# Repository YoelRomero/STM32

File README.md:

https://digole.com/tools/PicturetoC_Hex_converter.php
ILI_9341

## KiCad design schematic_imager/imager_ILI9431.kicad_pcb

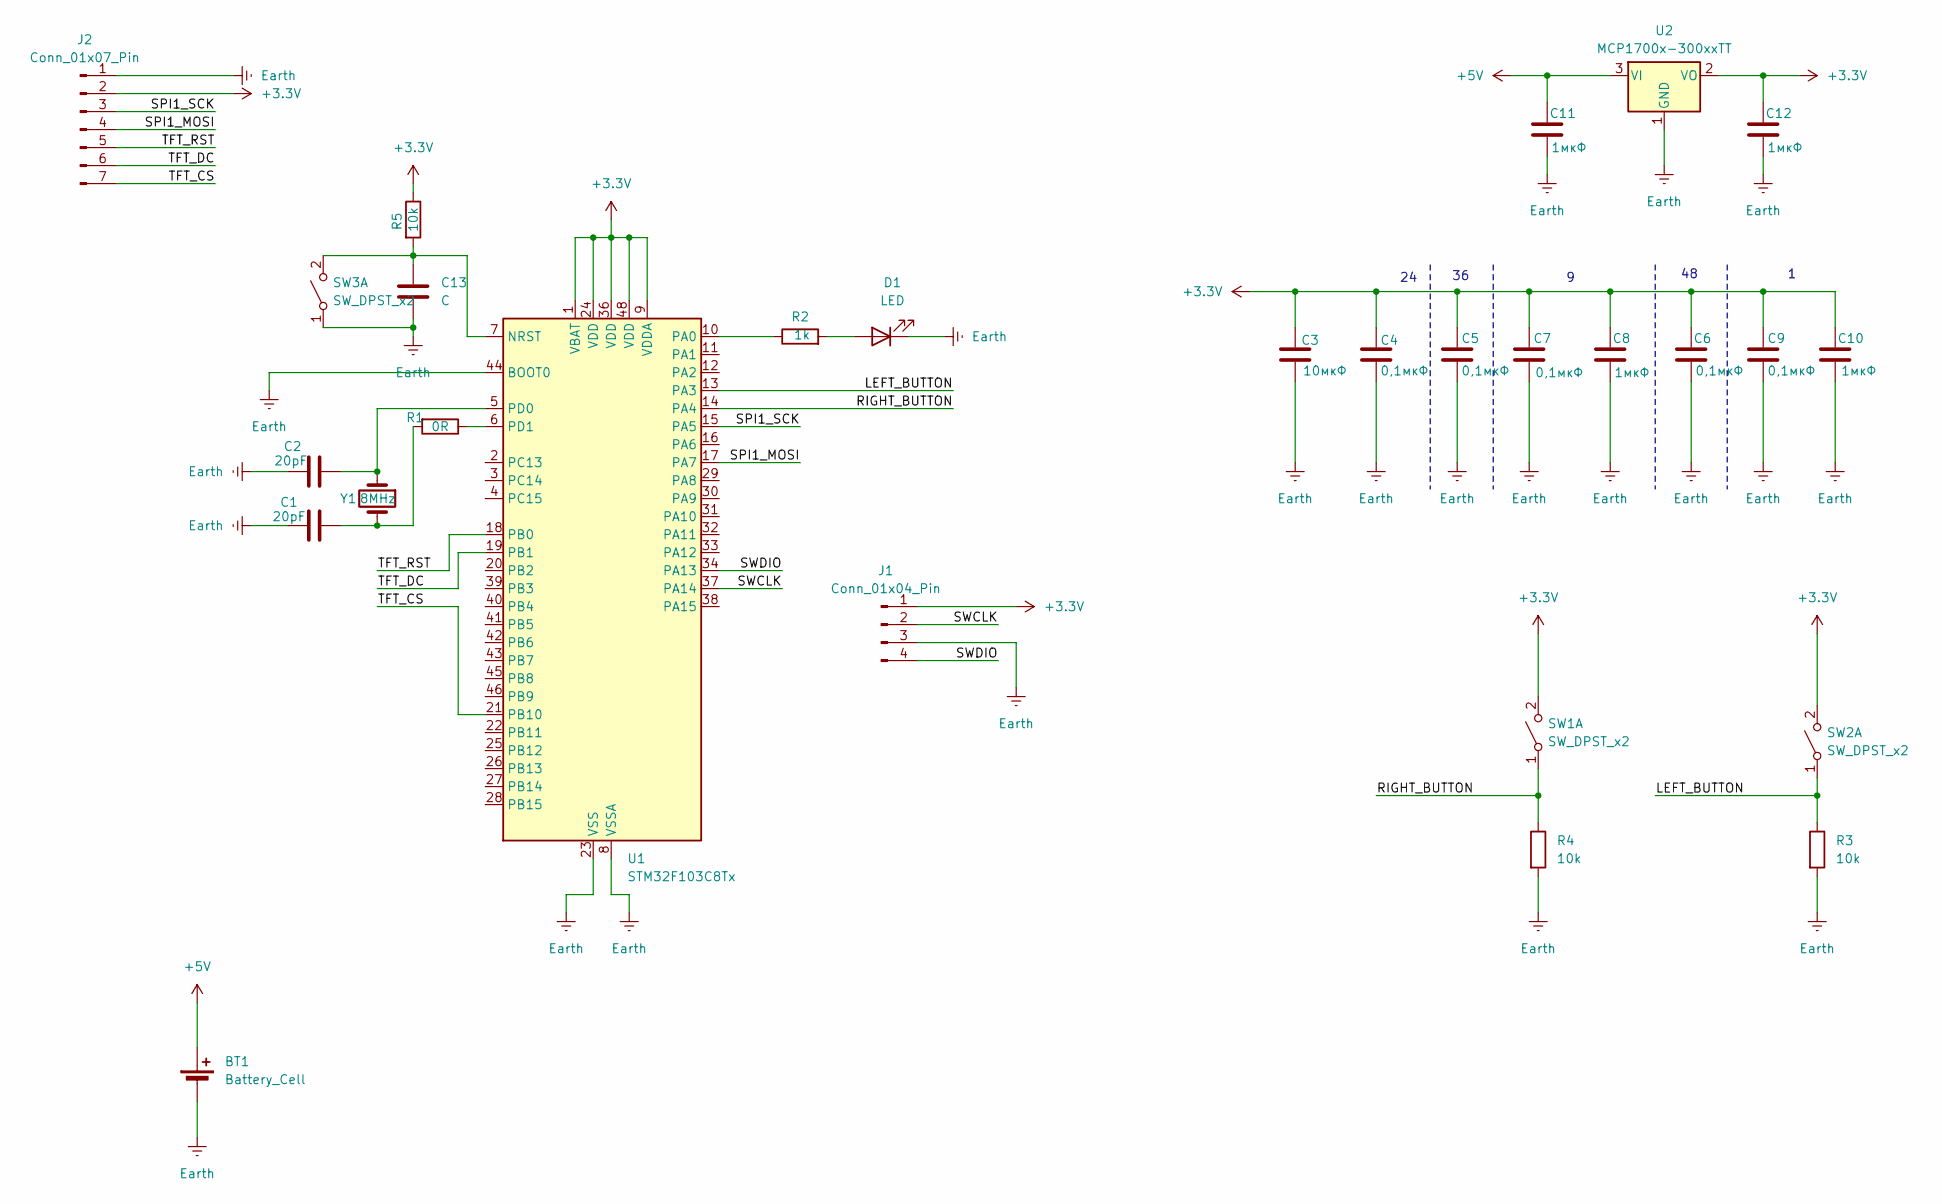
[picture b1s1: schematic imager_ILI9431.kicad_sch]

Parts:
BT1: Battery_Cell; PinHeader_1x02_P2.54mm_Vertical
C1, C2: 20pF; C_0402_1005Metric
C3: 10мкФ; C_0402_1005Metric
C4, C5, C6, C7, C9: 0,1мкФ; C_0402_1005Metric
C8, C10, C11, C12: 1мкФ; C_0402_1005Metric
C13: C; C_0402_1005Metric
D1: LED; LED_0402_1005Metric_Pad0.77x0.64mm_HandSolder
J1: Conn_01x04_Pin; PinHeader_1x04_P2.54mm_Vertical
J2: Conn_01x07_Pin; PinSocket_1x07_P2.54mm_Vertical
R1: 0R; R_0402_1005Metric_Pad0.72x0.64mm_HandSolder
R2: 1k; R_0402_1005Metric_Pad0.72x0.64mm_HandSolder
R3, R4, R5: 10k; R_0402_1005Metric_Pad0.72x0.64mm_HandSolder
SW1, SW2: SW_DPST_x2; PinHeader_1x02_P2.54mm_Vertical
SW3: SW_DPST_x2; SW_SPST_CK_KXT3
U1: STM32F103C8Tx; LQFP-48_7x7mm_P0.5mm
U2: MCP1700x-300xxTT; SOT-23
Y1: 8MHz; Crystal_SMD_HC49-SD_HandSoldering

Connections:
+3.3V: C3.1, C4.1, C5.1, C6.1, C7.1, C8.1, C9.1, C10.1, C12.1, J1.1, J2.2, R5.1, SW1.2 (B), SW2.2 (B), U1.1 (VBAT), U1.9 (VDDA), U1.24 (VDD), U1.36 (VDD), U1.48 (VDD), U2.2 (VO)
+5V: BT1.1 (+), C11.1, U2.3 (VI)
/LEFT_BUTTON: R3.1, SW2.1 (A), U1.13 (PA3)
/RIGHT_BUTTON: R4.1, SW1.1 (A), U1.14 (PA4)
/SPI1_MOSI: J2.4, U1.17 (PA7)
/SPI1_SCK: J2.3, U1.15 (PA5)
/SWCLK: J1.2, U1.37 (PA14)
/SWDIO: J1.4, U1.34 (PA13)
/TFT_CS: J2.7, U1.21 (PB10)
/TFT_DC: J2.6, U1.19 (PB1)
/TFT_RST: J2.5, U1.18 (PB0)
Earth: BT1.2 (-), C1.1, C2.1, C3.2, C4.2, C5.2, C6.2, C7.2, C8.2, C9.2, C10.2, C11.2, C12.2, C13.2, D1.1 (K), J1.3, J2.1, R3.2, R4.2, SW3.1 (A), U1.8 (VSSA), U1.23 (VSS), U1.35 (VSS), U1.44 (BOOT0), U1.47 (VSS), U2.1 (GND)
unnamed: C1.2, R1.2, Y1.2
unnamed: D1.2 (A), R2.2
unnamed: C13.1, R5.2, SW3.2 (B), U1.7 (NRST)
unnamed: R2.1, U1.10 (PA0)
unnamed: C2.2, U1.5 (PD0), Y1.1
unnamed: R1.1, U1.6 (PD1)

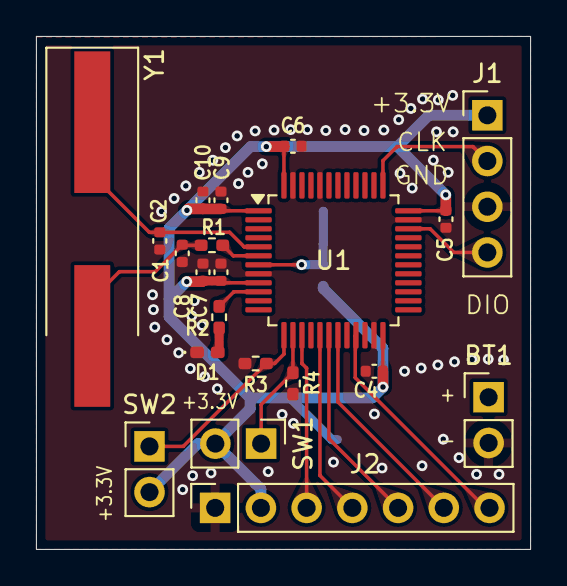
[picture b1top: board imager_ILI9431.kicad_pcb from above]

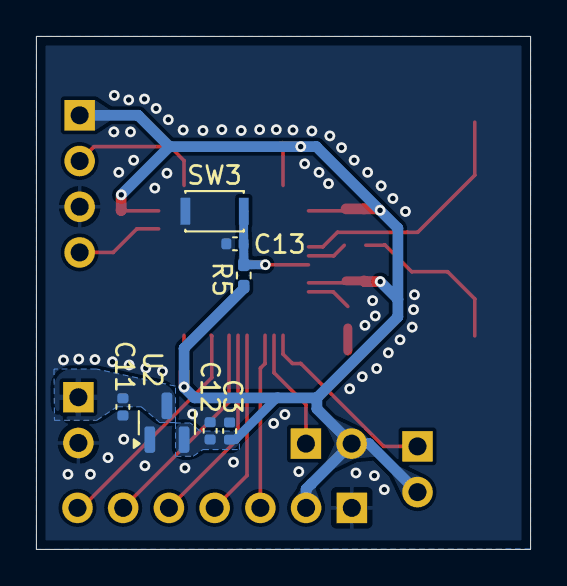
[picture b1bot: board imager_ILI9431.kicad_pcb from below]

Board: 2 copper layers, 27.5 x 28.5 mm, 28 parts (7 on the bottom side), 18 nets.

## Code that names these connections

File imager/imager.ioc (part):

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Mcu.Name=STM32F103C(8-B)Tx
Mcu.Package=LQFP48
Mcu.UserName=STM32F103C8Tx
PA13.Mode=Serial_Wire
PA13.Signal=SYS_JTMS-SWDIO
PA14.Mode=Serial_Wire
PA14.Signal=SYS_JTCK-SWCLK
PA3.GPIOParameters=GPIO_PuPd
PA3.GPIO_PuPd=GPIO_PULLUP
PA3.Signal=GPIO_Input
PA4.GPIOParameters=GPIO_PuPd
PA4.GPIO_PuPd=GPIO_PULLUP
PA4.Signal=GPIO_Input
PA5.Mode=TX_Only_Simplex_Unidirect_Master
PA5.Signal=SPI1_SCK
PA7.Mode=TX_Only_Simplex_Unidirect_Master
PA7.Signal=SPI1_MOSI
PB0.GPIOParameters=GPIO_Label
PB0.GPIO_Label=TFT_RST
PB0.Signal=GPIO_Output
PB1.GPIOParameters=GPIO_Label
PB1.GPIO_Label=TFT_DC
PB1.Signal=GPIO_Output
PB10.GPIOParameters=GPIO_Label
PB10.GPIO_Label=TFT_CS
PB10.Signal=GPIO_Output
PD0-OSC_IN.Mode=HSE-External-Oscillator
PD0-OSC_IN.Signal=RCC_OSC_IN
PD1-OSC_OUT.Mode=HSE-External-Oscillator
PD1-OSC_OUT.Signal=RCC_OSC_OUT
RCC.SYSCLKFreq_VALUE=72000000
RCC.SYSCLKSource=RCC_SYSCLKSOURCE_PLLCLK
board=custom

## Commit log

2024-12-18 Snake game for STM32F103C8T6 by Appliner corp
2024-12-18 Snake Game with snowflakes animation by Appliner corp
2024-12-18 Schematic PCB of Snake Game
